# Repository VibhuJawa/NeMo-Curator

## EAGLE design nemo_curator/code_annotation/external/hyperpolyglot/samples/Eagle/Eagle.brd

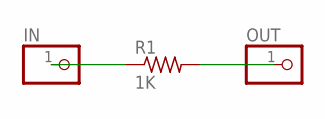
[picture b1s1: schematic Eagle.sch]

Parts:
IN: PINHD-1X1; 1X01
OUT: PINHD-1X1; 1X01
R1: 1K; R0805

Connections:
unnamed: IN.1, R1.1
unnamed: OUT.1, R1.2

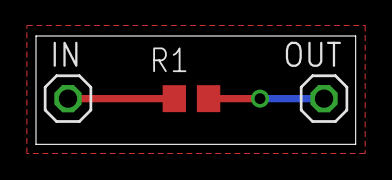
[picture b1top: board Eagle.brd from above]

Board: 2 copper layers, 17.8 x 6.0 mm, 3 parts (0 on the bottom side), 2 nets.

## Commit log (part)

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2026-06-18 build(deps): bump aiohttp from 3.14.0 to 3.14.1 (#2088)
    ---
    updated-dependencies:
    - dependency-name: aiohttp
    dependency-version: 3.14.1
    dependency-type: direct:production
    ...
2026-06-22 build(deps): bump jupyter-server from 2.18.0 to 2.20.0 (#2091)
    Bumps [jupyter-server](https://github.com/jupyter-server/jupyter_server) from 2.18.0 to 2.20.0.
    - [Release notes](https://github.com/jupyter-server/jupyter_server/releases)
    - [Changelog](https://github.com/jupyter-server/jupyter_server/blob/main/CHANGELOG.md)
    - [Commits](https://github.com/jupyter-server/jupyter_server/compare/v2.18.0...v2.20.0)
    ---
    updated-dependencies:
2026-06-22 build(deps): bump jupyterlab from 4.5.7 to 4.5.9 (#2099)
    ---
    updated-dependencies:
    - dependency-name: jupyterlab
    dependency-version: 4.5.9
    dependency-type: indirect
    ...
2026-06-22 feat(nemotron-parse): richer inference metrics, engine_kwargs passthrough, fanout stage spec (#2054)
2026-06-23 feat: support stage config overrides via with_ (#2086)
2026-06-23 build(deps): bump pydantic-settings from 2.12.0 to 2.14.2 (#2100)
    Bumps [pydantic-settings](https://github.com/pydantic/pydantic-settings) from 2.12.0 to 2.14.2.
    - [Release notes](https://github.com/pydantic/pydantic-settings/releases)
    - [Commits](https://github.com/pydantic/pydantic-settings/compare/v2.12.0...v2.14.2)
    ---
    updated-dependencies:
    - dependency-name: pydantic-settings
2026-06-23 Use reason flag for benchmark runs (#2103)
2026-06-23 fix(dynamo): multimodal chat processor, hybrid KV cache compat, subprocess env passthrough (#2053)
    * fix(dynamo): multimodal frontend processor, hybrid KV cache compat, subprocess env passthrough
    - Default Dynamo frontend to vLLM chat processor for multimodal models: the
    native-Rust processor serializes OpenAI multimodal content arrays instead of
    flattening them, corrupting prompts with pass-through chat templates
    - Skip --kv-events-config when user explicitly enables hybrid KV cache manager
    (disable_hybrid_kv_cache_manager=False); vLLM rejects both flags together even
2026-06-23 Fix NDD tutorial worker override (#2104)
2026-06-24 Reduce Lance IO checkpoint glue
2026-06-24 Trim Lance IO API surface
2026-06-24 Add Lance reader and checkpoint writers
2026-06-24 Move Lance checkpoint helpers to utils
2026-06-24 Document Lance public APIs
2026-06-24 Move Lance commit helpers out of writer
2026-06-24 Use Lance path as dataset name
2026-06-24 Move Lance blob restoration to reader
2026-06-24 Harden Lance IO checkpoint behavior
2026-06-24 Trim Lance integration code
2026-06-24 Remove Lance dataset name inference
2026-06-24 Scope Lance blob restore to v2
2026-06-24 Move Lance commit helpers under writer
2026-06-24 Clean up Lance writer utilities
2026-06-24 Address Lance review readability feedback
2026-06-24 Simplify Lance reader metadata handling
2026-06-24 Add Lance IO design diagram assets
2026-06-24 Add Lance IO driver worker boundary diagram
2026-06-24 benchmarking: detect parent schedule for nightly sessions (#2105)
2026-06-24 docs: clarify fuzzy dedup input blocksize (#2096)
    * docs: clarify fuzzy dedup input blocksize
    * docs: narrow fuzzy dedup note to main docs
    ---------
2026-06-24 Remove FlashAttn Deps (#2107)
    * remove fa
    * purge flash attn
    * docs change
    ---------
2026-06-24 [video] Remove model_does_preprocess (#2109)
    * refactor: remove model_does_preprocess flag across video processing stages
    - Eliminated the model_does_preprocess parameter from various components, including CaptionGenerationStage, CaptionPreparationStage, and QwenVL model, as all models now utilize vLLM's internal prepro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
    - Updated related documentation and examples to reflect this change.
    - Adjusted tests to ensure compatibility with the new processing model.
    * remove local video preprocess
    * address comment
2026-06-24 Add Lance reader stage
2026-06-24 Refine Lance reader option handling
2026-06-25 Add Lance writer stage
2026-06-25 Add Lance annotation writer stage
2026-06-25 fix: default workflow input extensions by filetype (#2045)
    * fix: default workflow input extensions by filetype
    * fix: validate default input file extensions
    * test: cover kmeans input file extension defaults
    * fix: address deduplication test failures
    * fix: use gpu markers for semantic tests
    ---------
2026-06-25 Add note about `InferenceServer` hang in `ndd_data_generation_example` tutorial (#2114)
    * add readme and hang fix options
    * add sentence
    * update wording
    ---------
2026-06-25 benchmarking: generate stable nightly session names (#2115)
2026-06-26 [Curator Video] Enable Ray Data stage fusion via cpus=1.0 in CPU video stages (#2110)
    * cpu=1
    * ray data specific
    * tests: cover RAY_NUM_CPUS guard and ray_data_num_cpus field
    ---------
2026-06-29 Add benchmark max timeout guard (#2116)
    * Add benchmark max timeout guard
    * Add max timeout boundary tests
    * Run benchmark runner tests in CI
    ---------
2026-06-29 Add CC Index URL list tutorial
2026-06-30 chore: Bump to 1.3.0 (#2140)
2026-06-30 Split CC index URL tutorial phases
2026-06-30 Refactor CC index URL tutorial modules
2026-06-30 Collapse CC index tutorial helpers
2026-06-30 Split CC index filegroup helpers
2026-06-30 build(deps): bump python-dotenv from 1.2.1 to 1.2.2 (#2117)
    Bumps [python-dotenv](https://github.com/theskumar/python-dotenv) from 1.2.1 to 1.2.2.
    - [Release notes](https://github.com/theskumar/python-dotenv/releases)
    - [Changelog](https://github.com/theskumar/python-dotenv/blob/main/CHANGELOG.md)
    - [Commits](https://github.com/theskumar/python-dotenv/compare/v1.2.1...v1.2.2)
    ---
    updated-dependencies:
2026-06-30 Pipeline resumability via source-level counter checkpointing (#2063)
    Opt-in pipeline resumability via Pipeline.run(checkpoint_path=...). A detached, namespaced Ray actor tracks per-source completion using a source-level in-flight counter, persisted to per-writer LMDB 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
    The pipeline owns the Ray session around the actor via 'with ray.init()' against a pre-existing cluster (RayClient), kept un-nested from the executor's own ray.init so executor env vars still propaga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
